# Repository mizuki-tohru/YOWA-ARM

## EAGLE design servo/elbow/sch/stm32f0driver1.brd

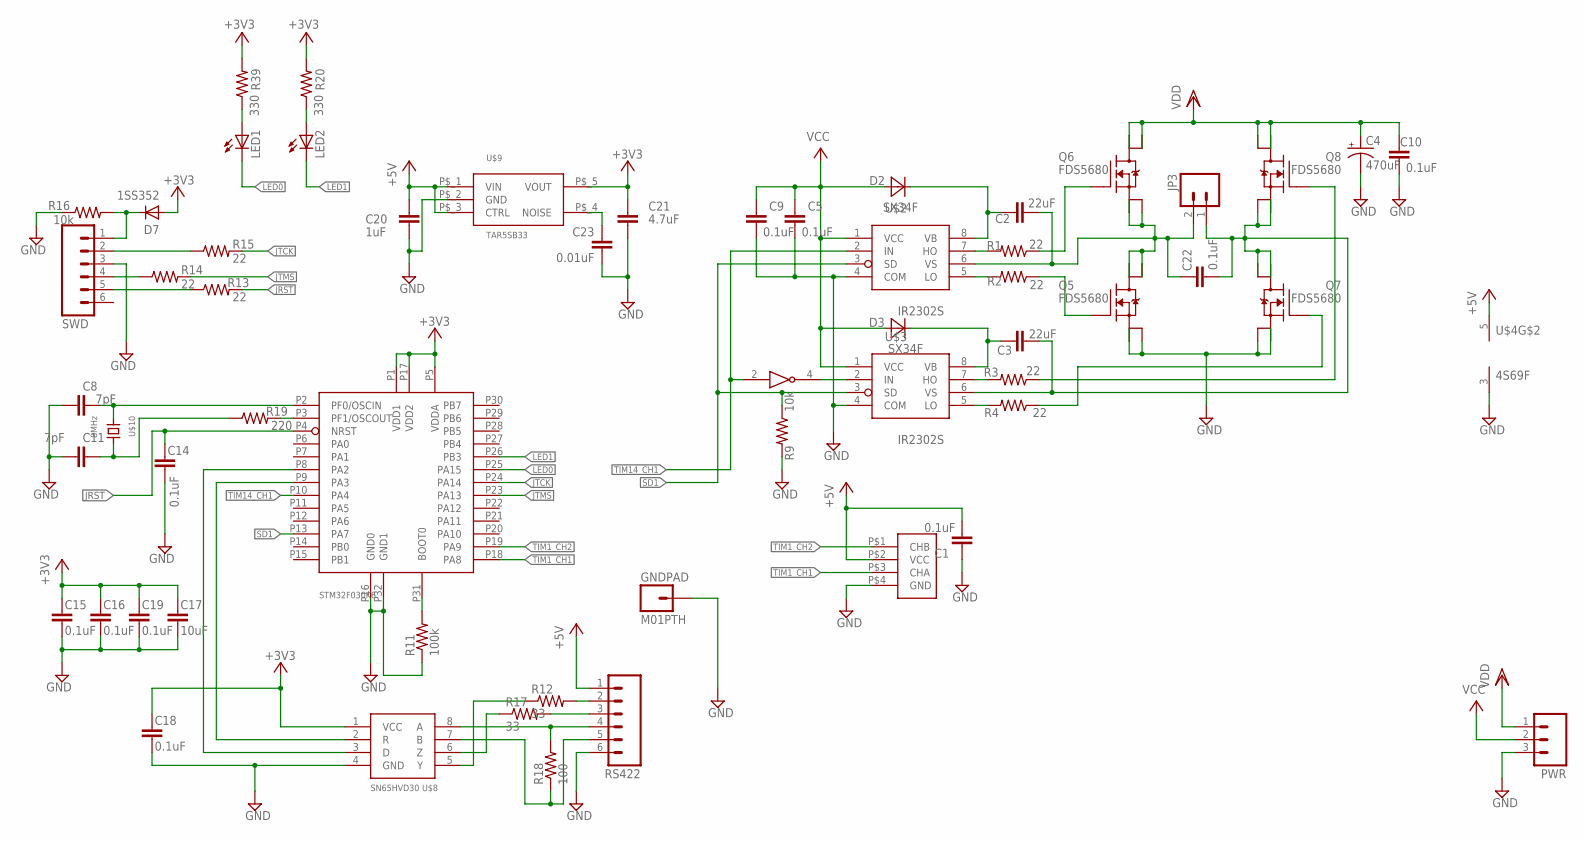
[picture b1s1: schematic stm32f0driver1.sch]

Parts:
C1, C5, C9, C10, C22: 0.1uF; C0603
C2, C3: 22uF; C3225
C4: 470uF; E5-10,5
C8, C11: 7pF; C0603
C14, C15, C16, C18, C19: 0.1uF; C1608
C17: 10uF; C3216
C20: 1uF; C2012
C21: 4.7uF; C2012
C23: 0.01uF; C0603
D2, D3: SX34F; SMA
D7: 1SS352; SOD-323
GNDPAD: M01PTH; 1X01
JP3: M02PTH3; 1X02_LONGPADS
LED1, LED2: LED0603; LED-0603
PWR: M03LONGPADS; 1X03_LONGPADS
Q5, Q6, Q7, Q8: FDS5680; 1206-8CHIP-FET
R1, R2, R3, R4, R13, R14, R15: 22; R0603
R9, R16: 10k; R0603
R11: 100k; R0603
R12, R17: 33; R0603
R18: 100; R0603
R19: 220; R0603
R20, R39: 330; R0603
RS422: M06SIP; 1X06
SWD: M06SIP; 1X06
U$1: HEDS9701-C54; HEDS9701
U$2, U$3: IR2302S; SO8
U$4: 4S69F; SOT23-5
U$7: STM32F030K6; LQFP32
U$8: SN65HVD30; SO8
U$9: TAR5SB33
U$10: 8MHz; SMD5032

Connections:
+3V3: C15.1, C16.1, C17.1, C18.1, C19.1, C21.1, D7.2 (A), R20.2, R39.2, U$7.P1 (VDD1), U$7.P5 (VDDA), U$7.P17 (VDD2), U$8.1 (VCC), U$9.P$_5 (VOUT)
+5V: C1.2, C20.1, RS422.1, U$1.P$2 (VCC), U$4.5 (V+), U$9.P$_1 (VIN), U$9.P$_3 (CTRL)
GND: C1.1, C4.-, C5.2, C8.2, C9.2, C10.2, C11.2, C14.2, C15.2, C16.2, C17.2, C18.2, C19.2, C20.2, C21.2, C23.2, GNDPAD.1, PWR.3, Q5.1 (S), Q5.2 (S1), Q5.3 (S2), Q7.1 (S), Q7.2 (S1), Q7.3 (S2), R9.2, R11.1, R16.1, RS422.6, SWD.3, U$1.P$4 (GND), U$2.4 (COM), U$3.4 (COM), U$4.3 (V-), U$7.P16 (GND0), U$7.P32 (GND1), U$8.4 (GND), U$9.P$_2 (GND)
JRST: C14.1, R13.2, U$7.P4 (NRST)
JTCK: R15.2, U$7.P24 (PA14)
JTMS: R14.2, U$7.P23 (PA13)
LED0: LED1.C, U$7.P25 (PA15)
LED1: LED2.C, U$7.P26 (PB3)
unnamed: C3.1, D3.C, U$3.8 (VB)
unnamed: C3.2, C22.2, JP3.1, Q7.5 (D), Q7.6 (D1), Q7.7 (D2), Q7.8 (D3), Q8.1 (S), Q8.2 (S1), Q8.3 (S2), U$3.6 (VS)
unnamed: C2.2, C22.1, JP3.2, Q5.5 (D), Q5.6 (D1), Q5.7 (D2), Q5.8 (D3), Q6.1 (S), Q6.2 (S1), Q6.3 (S2), U$2.6 (VS)
unnamed: C2.1, D2.C, U$2.8 (VB)
unnamed: R1.2, U$2.7 (HO)
unnamed: R19.2, U$7.P3 (PF1/OSCOUT)
unnamed: LED1.A, R39.1
unnamed: R2.2, U$2.5 (LO)
unnamed: R3.2, U$3.7 (HO)
unnamed: R4.2, U$3.5 (LO)
unnamed: Q6.4 (G), R1.1
unnamed: Q8.4 (G), R3.1
unnamed: C11.1, R19.1, U$10.P2
unnamed: Q7.4 (G), R4.1
unnamed: C8.1, U$7.P2 (PF0/OSCIN), U$10.P1
unnamed: D7.1 (C), R16.2, SWD.1
unnamed: LED2.A, R20.1
unnamed: U$3.2 (IN), U$4.4
unnamed: C23.1, U$9.P$_4 (NOISE)
unnamed: Q5.4 (G), R2.1
unnamed: R11.2, U$7.P31 (BOOT0)
unnamed: R15.1, SWD.2
unnamed: R14.1, SWD.4
unnamed: R13.1, SWD.5
unnamed: R12.2, RS422.2
unnamed: R17.2, RS422.3
unnamed: R12.1, U$8.5 (Y)
unnamed: R18.2, RS422.4, U$8.8 (A)
unnamed: R18.1, RS422.5, U$8.7 (B)
unnamed: R17.1, U$8.6 (Z)
unnamed: U$7.P8 (PA2), U$8.3 (D)
unnamed: U$7.P9 (PA3), U$8.2 (R)
SD1: R9.1, U$2.3 (SD), U$3.3 (SD), U$7.P13 (PA7)
TIM1_CH1: U$1.P$3 (CHA), U$7.P18 (PA8)
TIM1_CH2: U$1.P$1 (CHB), U$7.P19 (PA9)
TIM14_CH1: U$2.2 (IN), U$4.2, U$7.P10 (PA4)
VCC: C5.1, C9.1, D2.A, D3.A, PWR.2, U$2.1 (VCC), U$3.1 (VCC)
VDD: C4.+, C10.1, PWR.1, Q6.5 (D), Q6.6 (D1), Q6.7 (D2), Q6.8 (D3), Q8.5 (D), Q8.6 (D1), Q8.7 (D2), Q8.8 (D3)

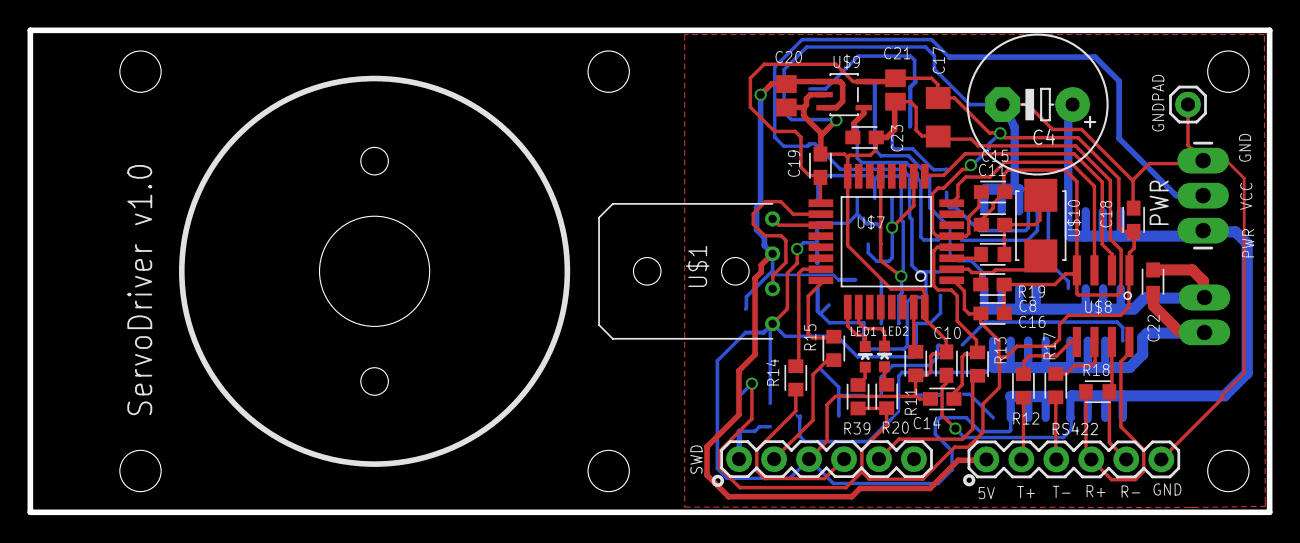
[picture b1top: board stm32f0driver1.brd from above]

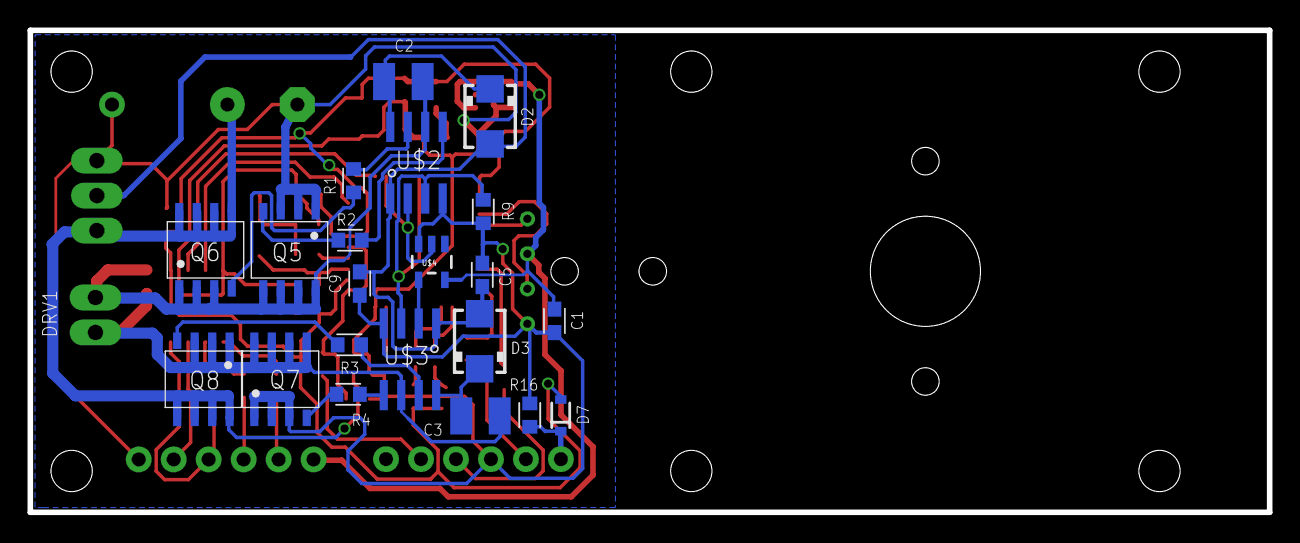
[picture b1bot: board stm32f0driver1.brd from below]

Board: 2 copper layers, 90.0 x 35.0 mm, 57 parts (22 on the bottom side), 46 nets.

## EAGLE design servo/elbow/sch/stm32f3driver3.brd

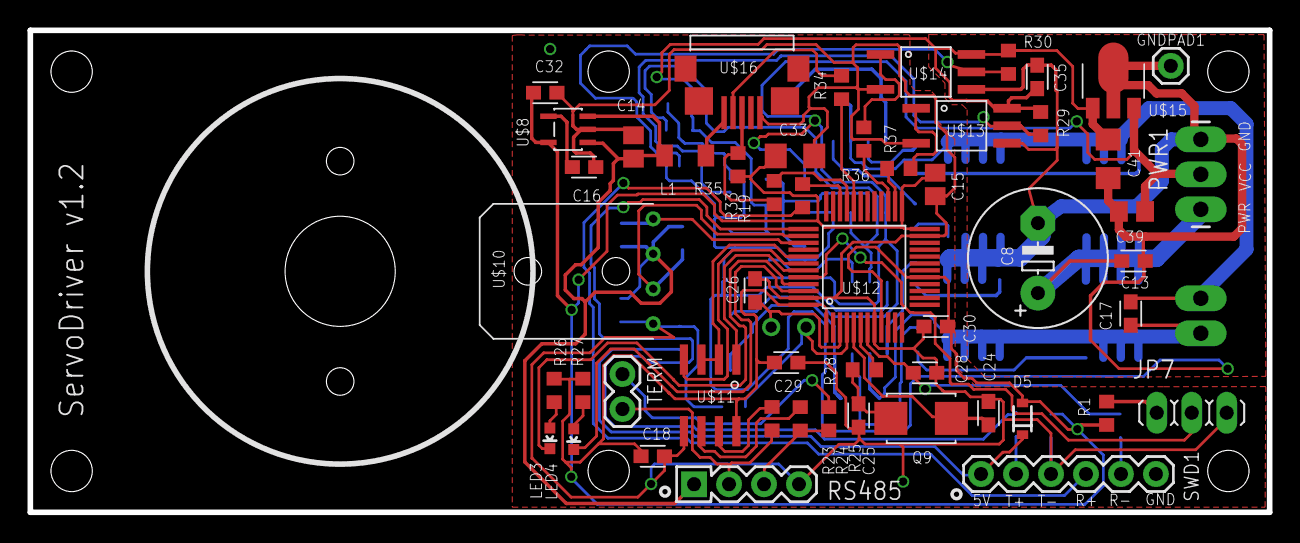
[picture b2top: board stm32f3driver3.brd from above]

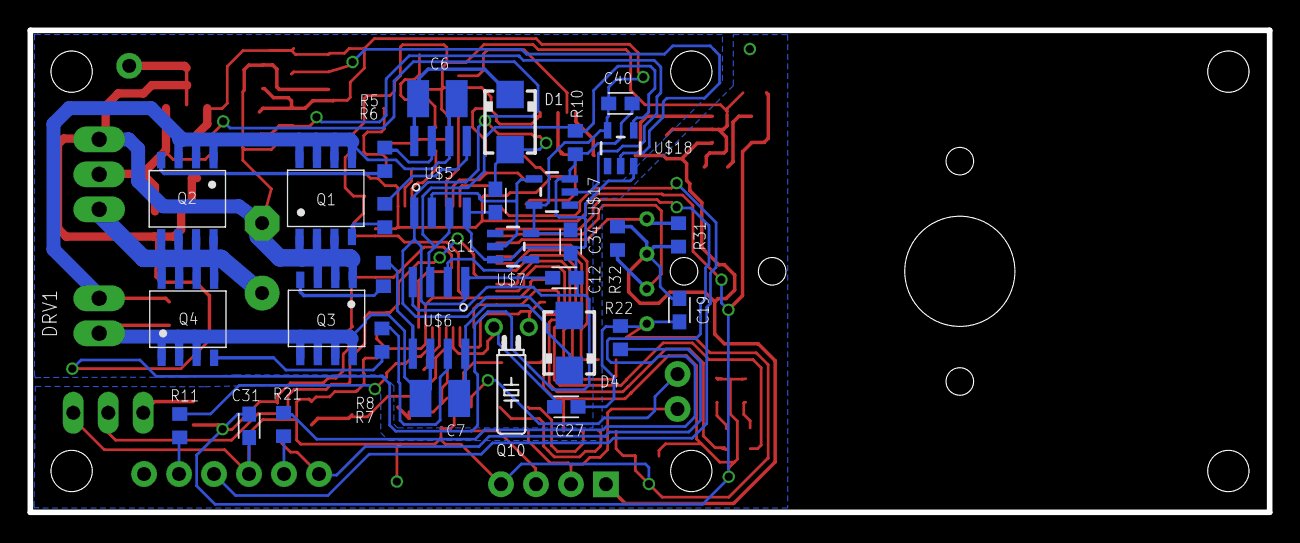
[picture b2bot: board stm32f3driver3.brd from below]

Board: 2 copper layers, 90.0 x 35.0 mm, 84 parts (31 on the bottom side), 62 nets.

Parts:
C6, C7: 22uF; C3225
C8: 470uF; E5-10,5
C11, C12, C13, C17, C19, C28, C34, C35, C40: 0.1uF; C0603
C14: 1uF; C2012
C15: 4.7uF; C2012
C16, C29, C30, C31, C32: 0.01uF; C0603
C18: 0.1uF; C1608
C24, C25: 7pF; C0603
C26, C27: 6.8pF; C0603
C33, C41: 10uF; C3216
C39: 0.33uF; C0805
D1, D4: SX34F; SMA
D5: 1SS352; SOD-323
GNDPAD1: M01PTH; 1X01
JP1: 1X02_LONGPADS
JP7: 1X03
L1: L3216C
LED3, LED4: LED-0603
PWR1: 1X03_LONGPADS
Q1, Q2, Q3, Q4: FDS5680; 1206-8CHIP-FET
Q9: 8MHz; SMD5032
Q10: 32.768kHz; TC26H
R1, R10, R22: 10k; R0603
R5, R6, R7, R8, R11, R19, R21: 22; R0603
R23, R24: 33; R0603
R25: 100; R0603
R26, R27, R29, R30, R31, R32: 330; R0603
R28: 220; R0603
R33, R34: 27; R0603
R35: 1.5k; R0603
R36, R37: 470; R0603
RS485: 1X04
SWD1: 1X06
TERM: 1X02
U$5, U$6: IR2302S; SO8
U$7, U$17, U$18: 4S69F; SOT23-5
U$8: TAR5SB33
U$10: HEDS9701-C54; HEDS9701
U$11: SN65HVD3085; SO8
U$12: STM32F373C; TQFP48
U$13, U$14: ACPL-M60L; SO5
U$15: NJM78L05UA; SOT89
U$16: USB-MICROB; USB_MICROB

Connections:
+3V3: C15.1, C18.1, C29.1, C30.1, C31.1, C32.1, C33.1, D5.2, R1.2, R26.2, R27.2, R35.2, U$8.P$_5, U$11.8, U$12.P$1, U$12.P$9, U$12.P$17, U$12.P$24, U$12.P$25, U$12.P$48
+5V: C14.1, C19.2, L1.2, R31.2, R32.2, RS485.1, U$8.P$_1, U$8.P$_3, U$10.P$2
BOOT0: JP7.2, U$12.P$44
DGND: C14.2, C15.2, C16.2, C18.2, C19.1, C24.2, C25.2, C26.2, C27.2, C28.2, C29.2, C30.2, C31.2, C32.2, C33.2, JP7.1, R22.1, RS485.4, SWD1.3, U$8.P$_2, U$10.P$4, U$11.5, U$12.P$8, U$12.P$23, U$12.P$47, U$13.P$2, U$14.P$2, U$16.P$5
DRV_IN: U$5.2, U$7.2, U$17.4
GND: C8.-, C11.2, C12.2, C13.2, C34.2, C35.2, C39.2, C40.2, C41.2, GNDPAD1.1, PWR1.3, Q1.1, Q1.2, Q1.3, Q3.1, Q3.2, Q3.3, R10.2, U$5.4, U$6.4, U$7.3, U$13.P$3, U$14.P$3, U$15.2, U$15.2@1, U$17.3, U$18.3
JRST: C28.1, R11.2, U$12.P$7
JTCK: R21.2, U$12.P$37
JTMS: R19.2, U$12.P$34
LED0: LED3.C, U$12.P$45
LED1: LED4.C, U$12.P$46
unnamed: C7.1, D4.C, U$6.8
unnamed: C7.2, C17.2, JP1.1, Q3.5, Q3.6, Q3.7, Q3.8, Q4.1, Q4.2, Q4.3, U$6.6
unnamed: C6.2, C17.1, JP1.2, Q1.5, Q1.6, Q1.7, Q1.8, Q2.1, Q2.2, Q2.3, U$5.6
unnamed: C6.1, D1.C, U$5.8
unnamed: R5.2, U$5.7
unnamed: R6.2, U$5.5
unnamed: R7.2, U$6.7
unnamed: R8.2, U$6.5
unnamed: Q2.4, R5.1
unnamed: Q4.4, R7.1
unnamed: Q3.4, R8.1
unnamed: U$6.2, U$7.4
unnamed: Q1.4, R6.1
unnamed: D5.1, R22.2, SWD1.1
unnamed: R21.1, SWD1.2
unnamed: R19.1, SWD1.4
unnamed: R11.1, SWD1.5
unnamed: C16.1, U$8.P$_4
unnamed: LED3.A, R26.1
unnamed: LED4.A, R27.1
unnamed: R23.1, U$11.7
unnamed: R24.1, U$11.6
unnamed: R24.2, R25.1, RS485.3
unnamed: R23.2, RS485.2, TERM.2
unnamed: R25.2, TERM.1
unnamed: R28.1, U$12.P$6
unnamed: C25.1, Q9.P1, R28.2
unnamed: C24.1, Q9.P2, U$12.P$5
unnamed: C27.1, Q10.2, U$12.P$4
unnamed: C26.1, Q10.1, U$12.P$3
unnamed: R34.2, U$16.P$2
unnamed: R33.2, R35.1, U$16.P$3
unnamed: L1.1, U$16.P$1
unnamed: R29.1, U$13.P$4, U$17.2
unnamed: R30.1, U$14.P$4, U$18.2
unnamed: R37.1, U$14.P$1
unnamed: R36.1, U$13.P$1
unnamed: JP7.3, R1.1
SD1: R37.2, U$12.P$27
SD_IN: R10.1, U$5.3, U$6.3, U$18.4
TIM2_CH1: R32.1, U$10.P$3, U$12.P$38
TIM2_CH2: R31.1, U$10.P$1, U$12.P$39
TIM12_CH1: R36.2, U$12.P$26
U1ENA: U$11.2, U$11.3, U$12.P$41
U1RX: U$11.1, U$12.P$43
U1TX: U$11.4, U$12.P$42
USBDM: R34.1, U$12.P$32
USBDP: R33.1, U$12.P$33
VCC: C11.1, C12.1, C39.1, D1.A, D4.A, PWR1.2, U$5.1, U$6.1, U$15.3
VCC/2: C34.1, C35.1, C40.1, C41.1, R29.2, R30.2, U$7.5, U$13.P$5, U$14.P$5, U$15.1, U$17.5, U$18.5
VDD: C8.+, C13.1, PWR1.1, Q2.5, Q2.6, Q2.7, Q2.8, Q4.5, Q4.6, Q4.7, Q4.8

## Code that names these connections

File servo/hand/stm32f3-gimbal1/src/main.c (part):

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#include "accTask.h"

// IO Pin
// PA2  DTIN1  I/O IN
// PA3  DTIN2  I/O IN
// PA4  DTIN3  I/O IN
// PA5  AINT   I/O IN
// PA6  GINT   I/O IN
// PA9  SCL2   AF4
// PA10 SDA2   AF4
// PA11 USB    AF14
// PA12 USB    AF14
// PA13 JTMS   AF0
// PA14 JTCK   AF0
// PA15 TIM12_CH2 AF10   SERVO1
// PB0  JOY_X  ADC_IN8
// PB1  JOY_Y  ADC_IN9
// PB3  TIM2_CH2 AF1     SERVO2
// PB4  TIM3_CH1 AF2     SERVO3
// PB5  U1ENA  I/O OUT
// PB6  U1TX   AF7
// PB7  U1RX   AF7
// PB8  LED0   I/O OUT
// PB9  LED1   I/O OUT

/** @addtogroup Template_Project
  * @{
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	GPIO_PinAFConfig(GPIOA, GPIO_PinSource10, GPIO_AF_4);/*SDA2*/
	GPIO_PinAFConfig(GPIOA, GPIO_PinSource11, GPIO_AF_14);/*USB*/
	GPIO_PinAFConfig(GPIOA, GPIO_PinSource12, GPIO_AF_14);/*USB*/
	GPIO_PinAFConfig(GPIOA, GPIO_PinSource13, GPIO_AF_0);/*JTMS*/
	GPIO_PinAFConfig(GPIOA, GPIO_PinSource14, GPIO_AF_0);/*JTCK*/
	GPIO_PinAFConfig(GPIOA, GPIO_PinSource15, GPIO_AF_10);/**/

	/* Enable the GPIO_B Clock */
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	GPIO_InitStructure.GPIO_PuPd = GPIO_PuPd_UP;
	GPIO_Init(GPIOB, &GPIO_InitStructure);
	
	GPIO_PinAFConfig(GPIOB, GPIO_PinSource3, GPIO_AF_1);/*TIM2_CH2*/
	GPIO_PinAFConfig(GPIOB, GPIO_PinSource4, GPIO_AF_2);/*TIM3_CH1*/
	GPIO_PinAFConfig(GPIOB, GPIO_PinSource6, GPIO_AF_7);/*U1_TX*/
	GPIO_PinAFConfig(GPIOB, GPIO_PinSource7, GPIO_AF_7);/*U1_RX*/
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
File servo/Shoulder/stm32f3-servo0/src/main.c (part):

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// IO Pin
// PA11 USB    AF14
// PA12 USB    AF14
// PA13 JTMS   AF0
// PA14 JTCK   AF0
// PA15 TIM2_CH1 AF1     ENCORDER
// PB3  TIM2_CH2 AF1     ENCORDER
// PB5  U1ENA  I/O OUT
// PB6  U1TX   AF7
// PB7  U1RX   AF7
// PB8  LED0   I/O OUT
// PB9  LED1   I/O OUT
// PB14 TIM12_CH1 AF9
// PB15 SD1    I/O OUT(TIM12_CH2 AF9)

/** @addtogroup Template_Project
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	
	GPIO_PinAFConfig(GPIOA, GPIO_PinSource11, GPIO_AF_14);/*USB*/
	GPIO_PinAFConfig(GPIOA, GPIO_PinSource12, GPIO_AF_14);/*USB*/
	GPIO_PinAFConfig(GPIOA, GPIO_PinSource13, GPIO_AF_0);/*JTMS*/
	GPIO_PinAFConfig(GPIOA, GPIO_PinSource14, GPIO_AF_0);/*JTCK*/
	GPIO_PinAFConfig(GPIOA, GPIO_PinSource15, GPIO_AF_1);/*TIM2_Ch1*/

	/* Enable the GPIO_B Clock */
	RCC_AHBPeriphClockCmd(RCC_AHBPeriph_GPIOB, ENABLE);
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	GPIO_InitStructure.GPIO_PuPd = GPIO_PuPd_UP;
	GPIO_Init(GPIOB, &GPIO_InitStructure);
	
	GPIO_PinAFConfig(GPIOB, GPIO_PinSource3,  GPIO_AF_1);/*TIM2_CH2*/
	GPIO_PinAFConfig(GPIOB, GPIO_PinSource6,  GPIO_AF_7);/*U1_TX*/
	GPIO_PinAFConfig(GPIOB, GPIO_PinSource7,  GPIO_AF_7);/*U1_RX*/
	GPIO_PinAFConfig(GPIOB, GPIO_PinSource14, GPIO_AF_9);/*TIM12_CH1*/
//	GPIO_PinAFConfig(GPIOB, GPIO_PinSource15, GPIO_AF_9);/*TIM12_CH2*/
}

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
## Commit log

2014-06-08 first
2014-06-08 readme write
2015-08-11 Make Tokyo 2015 Var.
2015-08-11 file add

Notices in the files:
servo/Shoulder/stm32f3-servo0/src/main.c:
© COPYRIGHT 2012 STMicroelectronics
Licensed under MCD-ST Liberty SW License Agreement V2, (the "License");
(C) COPYRIGHT STMicroelectronics *****END OF FILE
parts and their libraries:
SparkFun: Licensing: CC v3.0 Share-Alike You are welcome to use this library for commercial purposes.
